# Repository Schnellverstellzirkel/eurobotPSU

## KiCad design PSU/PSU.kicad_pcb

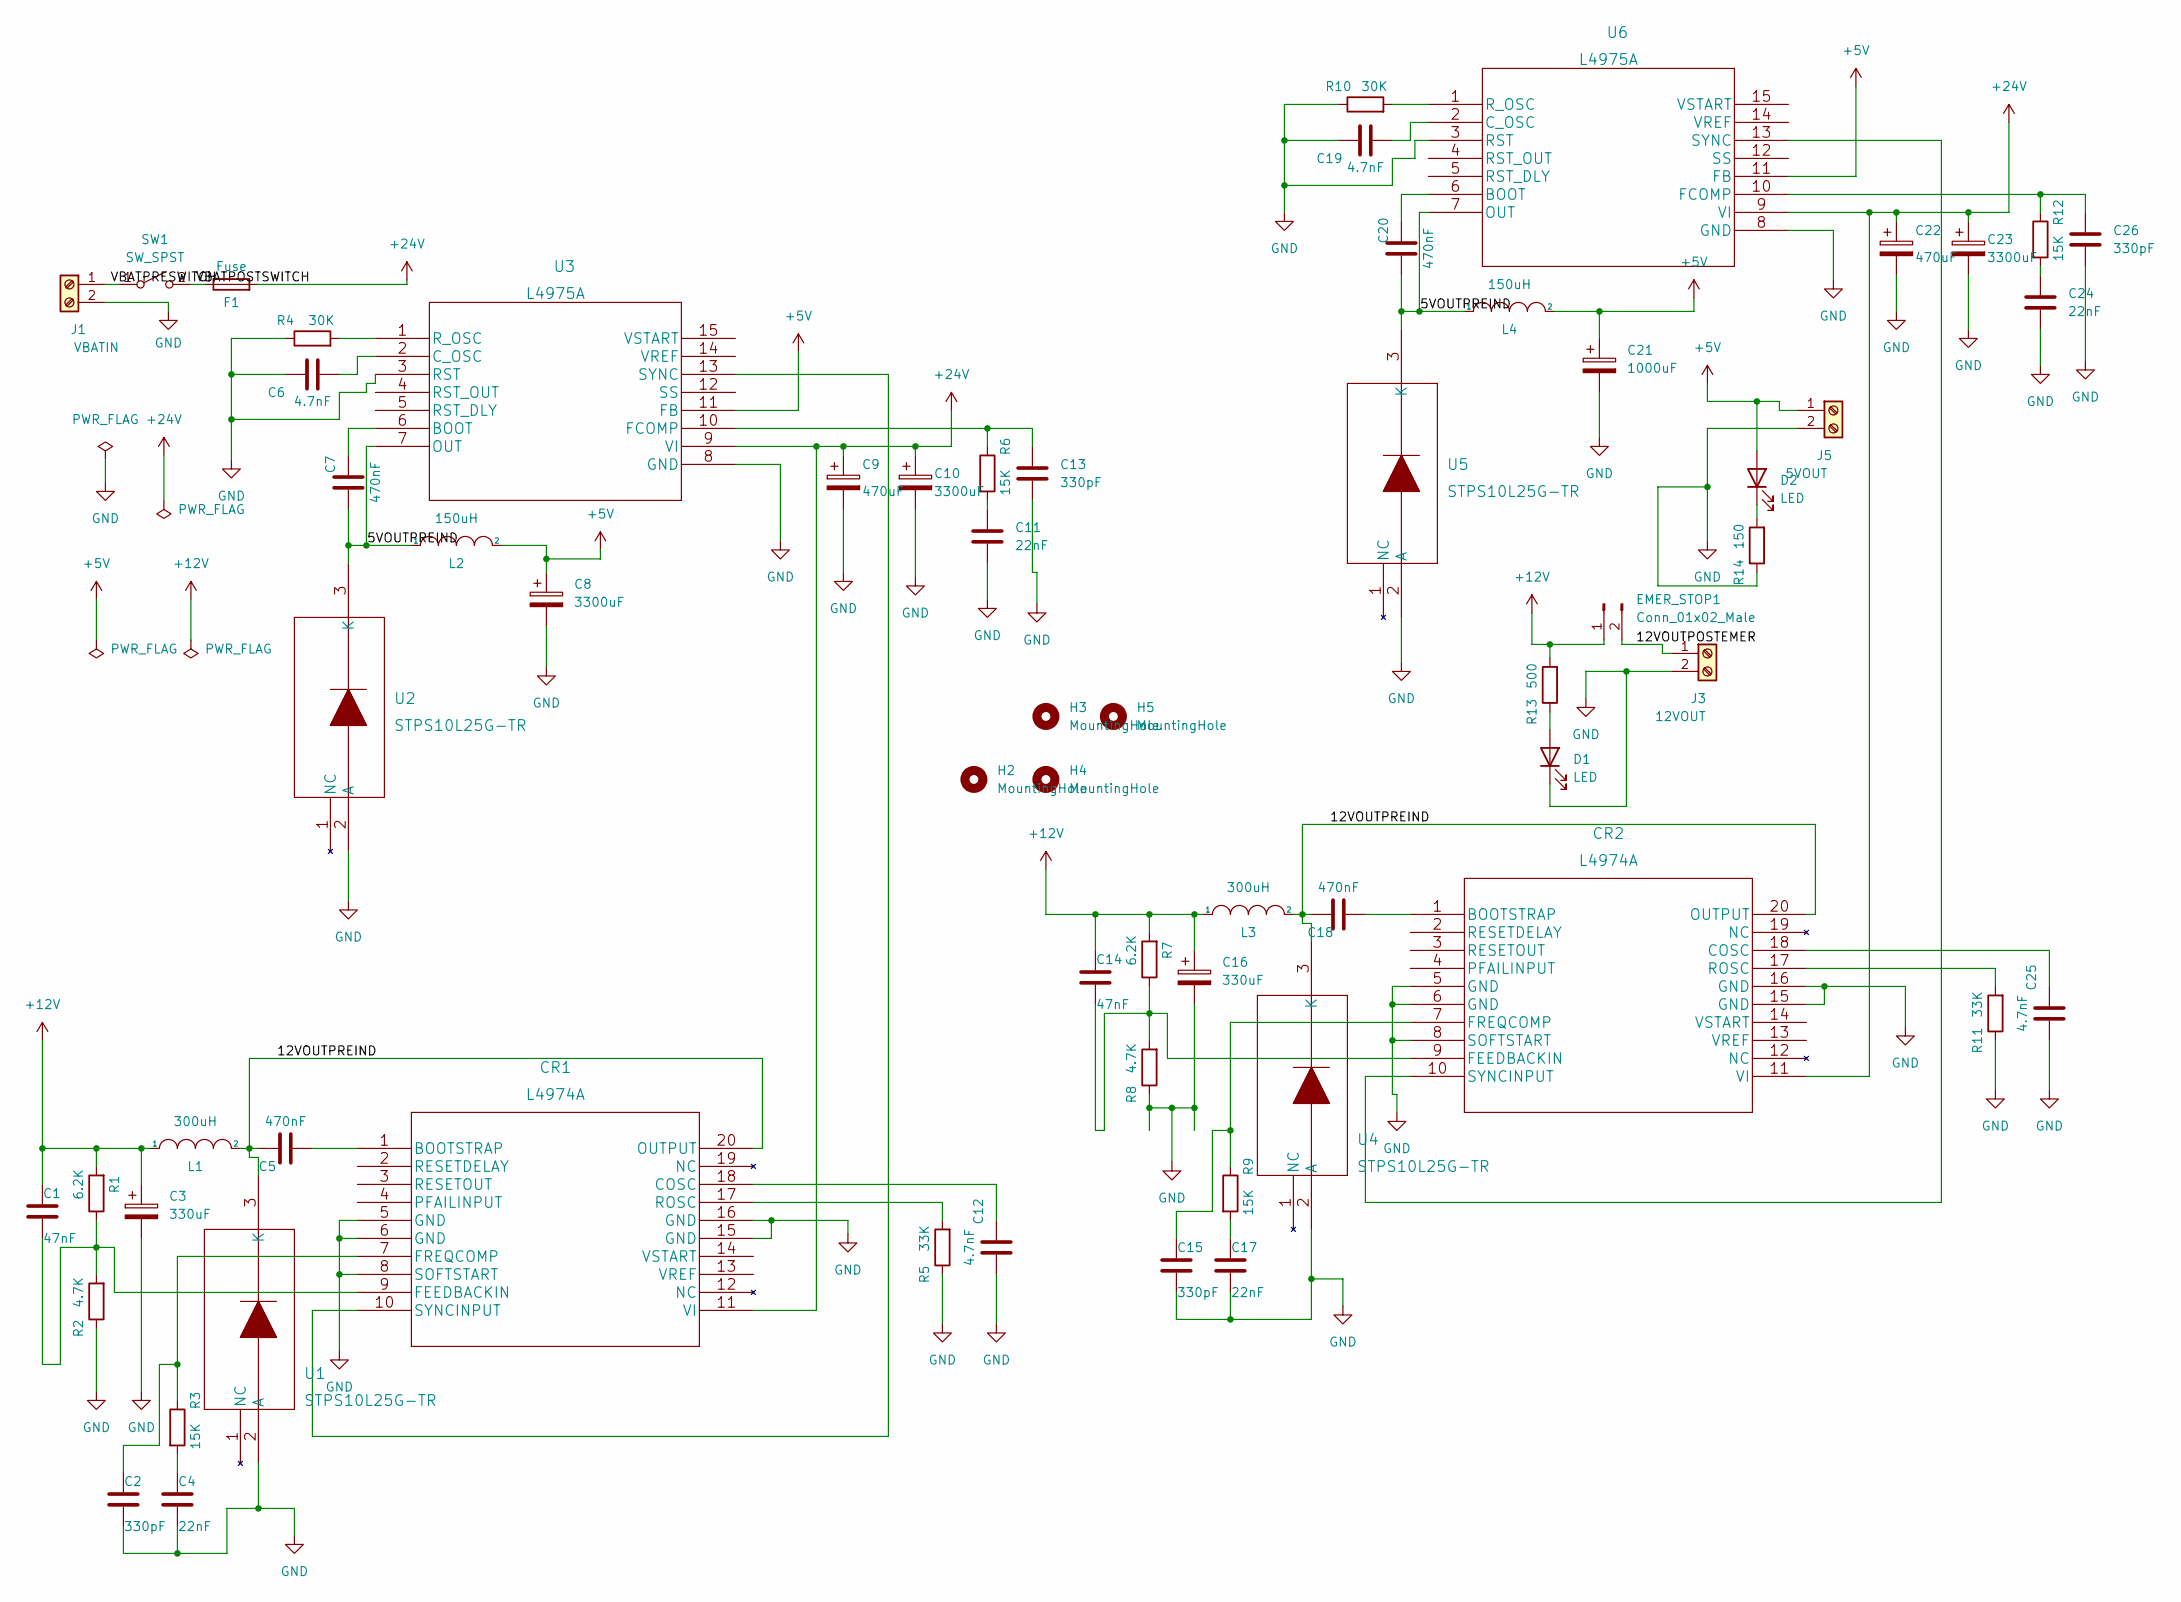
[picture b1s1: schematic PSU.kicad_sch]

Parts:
C1, C14: 47nF; C_0805_2012Metric
C2, C13, C15, C26: 330pF; C_0805_2012Metric
C3, C16: 330uF; CP_Radial_D13.0mm_P5.00mm
C4, C11, C17, C24: 22nF; C_0805_2012Metric
C5, C7, C18, C20: 470nF; C_0805_2012Metric
C6, C12, C19, C25: 4.7nF; C_0805_2012Metric
C8, C10, C23: 3300uF; CP_Radial_D13.0mm_P5.00mm
C9, C22: 470uF; CP_Radial_D13.0mm_P5.00mm
C21: 1000uF; CP_Radial_D13.0mm_P5.00mm
CR1, CR2: L4974A
D1, D2: LED; LED_D5.0mm
EMER_STOP1: Conn_01x02_Male; JST_VH_B2P-VH-B_1x02_P3.96mm_Vertical
F1: Fuse; Fuseholder_Littelfuse_445_030_series_5x20mm
H2, H3, H4, H5: MountingHole; MountingHole_3.2mm_M3
J1: VBATIN; TerminalBlock_Altech_AK300-2_P5.00mm
J3: 12VOUT; TerminalBlock_Altech_AK300-2_P5.00mm
J5: 5VOUT; TerminalBlock_Altech_AK300-2_P5.00mm
L1, L3: 300uH; L_Radial_D12.0mm_P10.00mm_Neosid_SD12_style1
L2, L4: 150uH; L_Radial_D12.0mm_P10.00mm_Neosid_SD12_style1
R1, R7: 6.2K; R_0805_2012Metric
R2, R8: 4.7K; R_0805_2012Metric
R3, R6, R9, R12: 15K; R_0805_2012Metric
R4, R10: 30K; R_0805_2012Metric
R5, R11: 33K; R_0805_2012Metric
R13: 500; R_0805_2012Metric
R14: 150; R_0805_2012Metric
SW1: SW_SPST; JST_VH_B2P-VH_1x02_P3.96mm_Vertical
U1, U2, U4, U5: STPS10L25G-TR
U3, U6: L4975A

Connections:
+5V: C8.1, C21.1, D2.2 (A), J5.1, L2.2, L4.2, U3.11 (FB), U6.11 (FB)
+12V: C1.1, C3.1, C14.1, C16.1, EMER_STOP1.1, L1.1, L3.1, R1.2, R7.2, R13.2
+24V: C9.1, C10.1, C22.1, C23.1, CR1.11 (VI), CR2.11 (VI), F1.2, U3.9 (VI), U6.9 (VI)
/5VOUTPREIND: C7.1, C20.1, L2.1, L4.1, U2.3 (K), U3.7 (OUT), U5.3 (K), U6.7 (OUT)
/12VOUTPOSTEMER: EMER_STOP1.2, J3.1
/12VOUTPREIND: C5.2, C18.2, CR1.20 (OUTPUT), CR2.20 (OUTPUT), L1.2, L3.2, U1.3 (K), U4.3 (K)
/VBATPOSTSWITCH: F1.1, SW1.2 (B)
/VBATPRESWITCH: J1.1, SW1.1 (A)
GND: C2.2, C3.2, C4.2, C6.1, C8.2, C9.2, C10.2, C11.2, C12.2, C13.2, C15.2, C16.2, C17.2, C19.1, C21.2, C22.2, C23.2, C24.2, C25.2, C26.2, CR1.5 (GND), CR1.6 (GND), CR1.8 (SOFTSTART), CR1.15 (GND), CR1.16 (GND), CR2.5 (GND), CR2.6 (GND), CR2.8 (SOFTSTART), CR2.15 (GND), CR2.16 (GND), D1.1 (K), J1.2, J3.2, J5.2, R2.1, R4.1, R5.1, R8.1, R10.1, R11.1, R14.1, U1.2 (A), U2.2 (A), U3.3 (RST), U3.8 (GND), U4.2 (A), U5.2 (A), U6.3 (RST), U6.8 (GND)
unnamed: C1.2, CR1.9 (FEEDBACKIN), R1.1, R2.2
unnamed: C2.1, CR1.7 (FREQCOMP), R3.1
unnamed: C4.1, R3.2
unnamed: C5.1, CR1.1 (BOOTSTRAP)
unnamed: C6.2, U3.2 (C_OSC)
unnamed: C7.2, U3.6 (BOOT)
unnamed: C11.1, R6.2
unnamed: C12.1, CR1.18 (COSC)
unnamed: C13.1, R6.1, U3.10 (FCOMP)
unnamed: C14.2, CR2.9 (FEEDBACKIN), R7.1, R8.2
unnamed: C15.1, CR2.7 (FREQCOMP), R9.1
unnamed: C17.1, R9.2
unnamed: C18.1, CR2.1 (BOOTSTRAP)
unnamed: C19.2, U6.2 (C_OSC)
unnamed: C20.2, U6.6 (BOOT)
unnamed: C24.1, R12.2
unnamed: C25.1, CR2.18 (COSC)
unnamed: C26.1, R12.1, U6.10 (FCOMP)
unnamed: CR1.10 (SYNCINPUT), U3.13 (SYNC)
unnamed: CR1.17 (ROSC), R5.2
unnamed: CR2.10 (SYNCINPUT), U6.13 (SYNC)
unnamed: CR2.17 (ROSC), R11.2
unnamed: D1.2 (A), R13.1
unnamed: D2.1 (K), R14.2
unnamed: R4.2, U3.1 (R_OSC)
unnamed: R10.2, U6.1 (R_OSC)

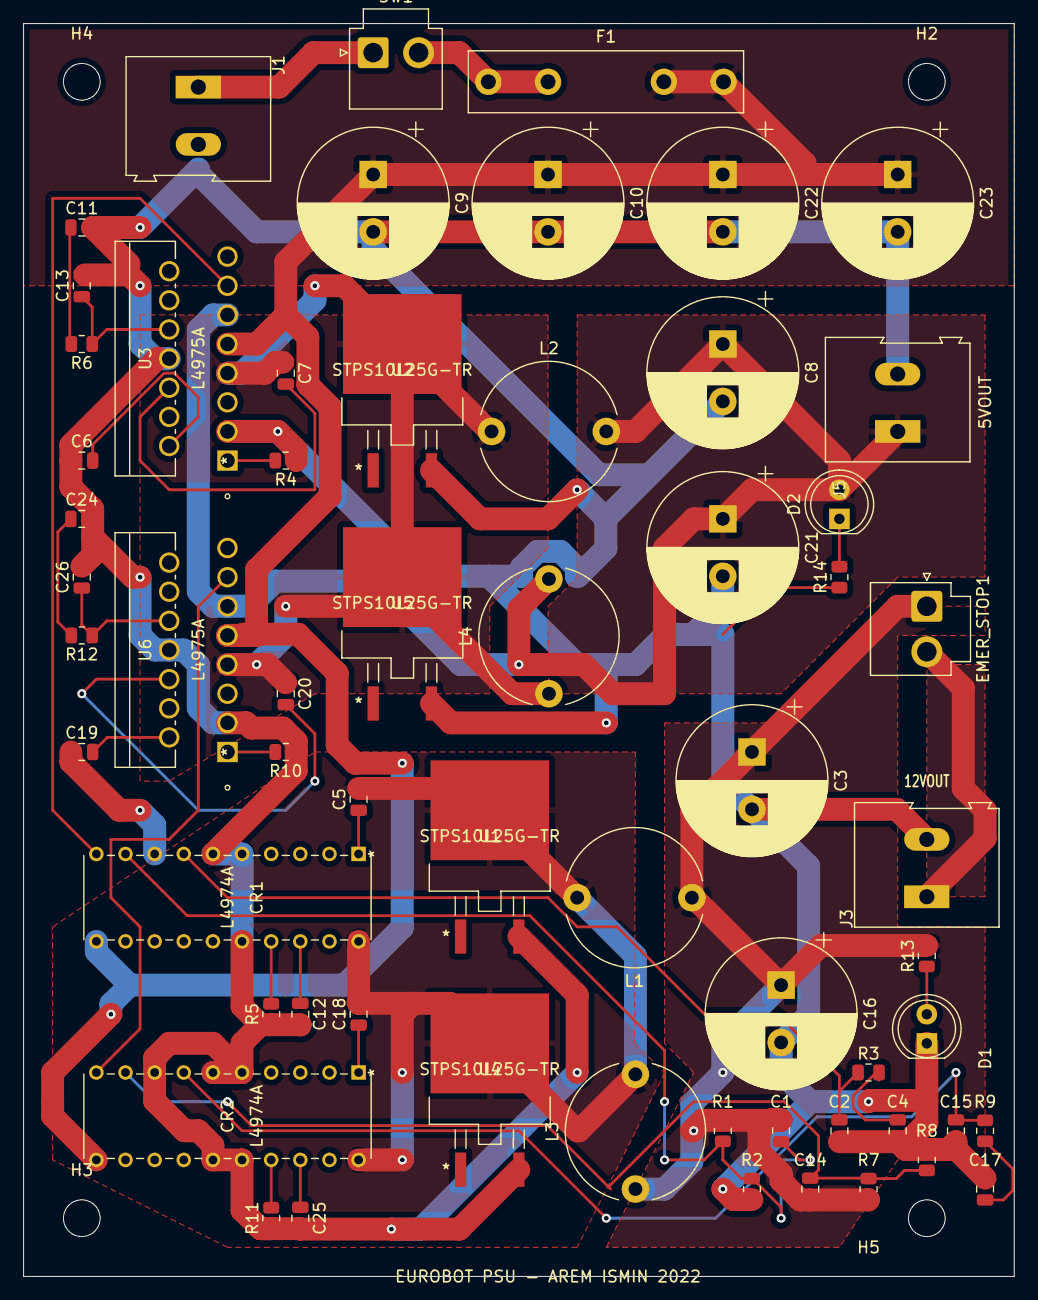
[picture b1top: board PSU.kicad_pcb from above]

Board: 2 copper layers, 86.4 x 109.2 mm, 64 parts (0 on the bottom side), 35 nets.

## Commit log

2022-02-13 Initial commit
    Creating the KiCad project and importing libraries for the ST components
2022-02-13 Unverified schematic
    Drawn the schematic, still need to double check connections. Footprints are yet to be set
2022-02-14 set footprints
    footprints were set for all components
2022-02-15 PCB placed and routed, more work to come
    still need to check what's wrong with the schottky footprints
2022-02-19 Revisited PCB
    - SMT resistors instead of THT
    - Added LEDs
    - Added emergency stop button connector
2022-02-19 Gerber files added
2022-02-23 Added switch and made space for inductors
2022-02-23 Final layout

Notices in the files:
parts and their libraries:
Copyright 2021 Accelerated Designs. All rights reserved.
